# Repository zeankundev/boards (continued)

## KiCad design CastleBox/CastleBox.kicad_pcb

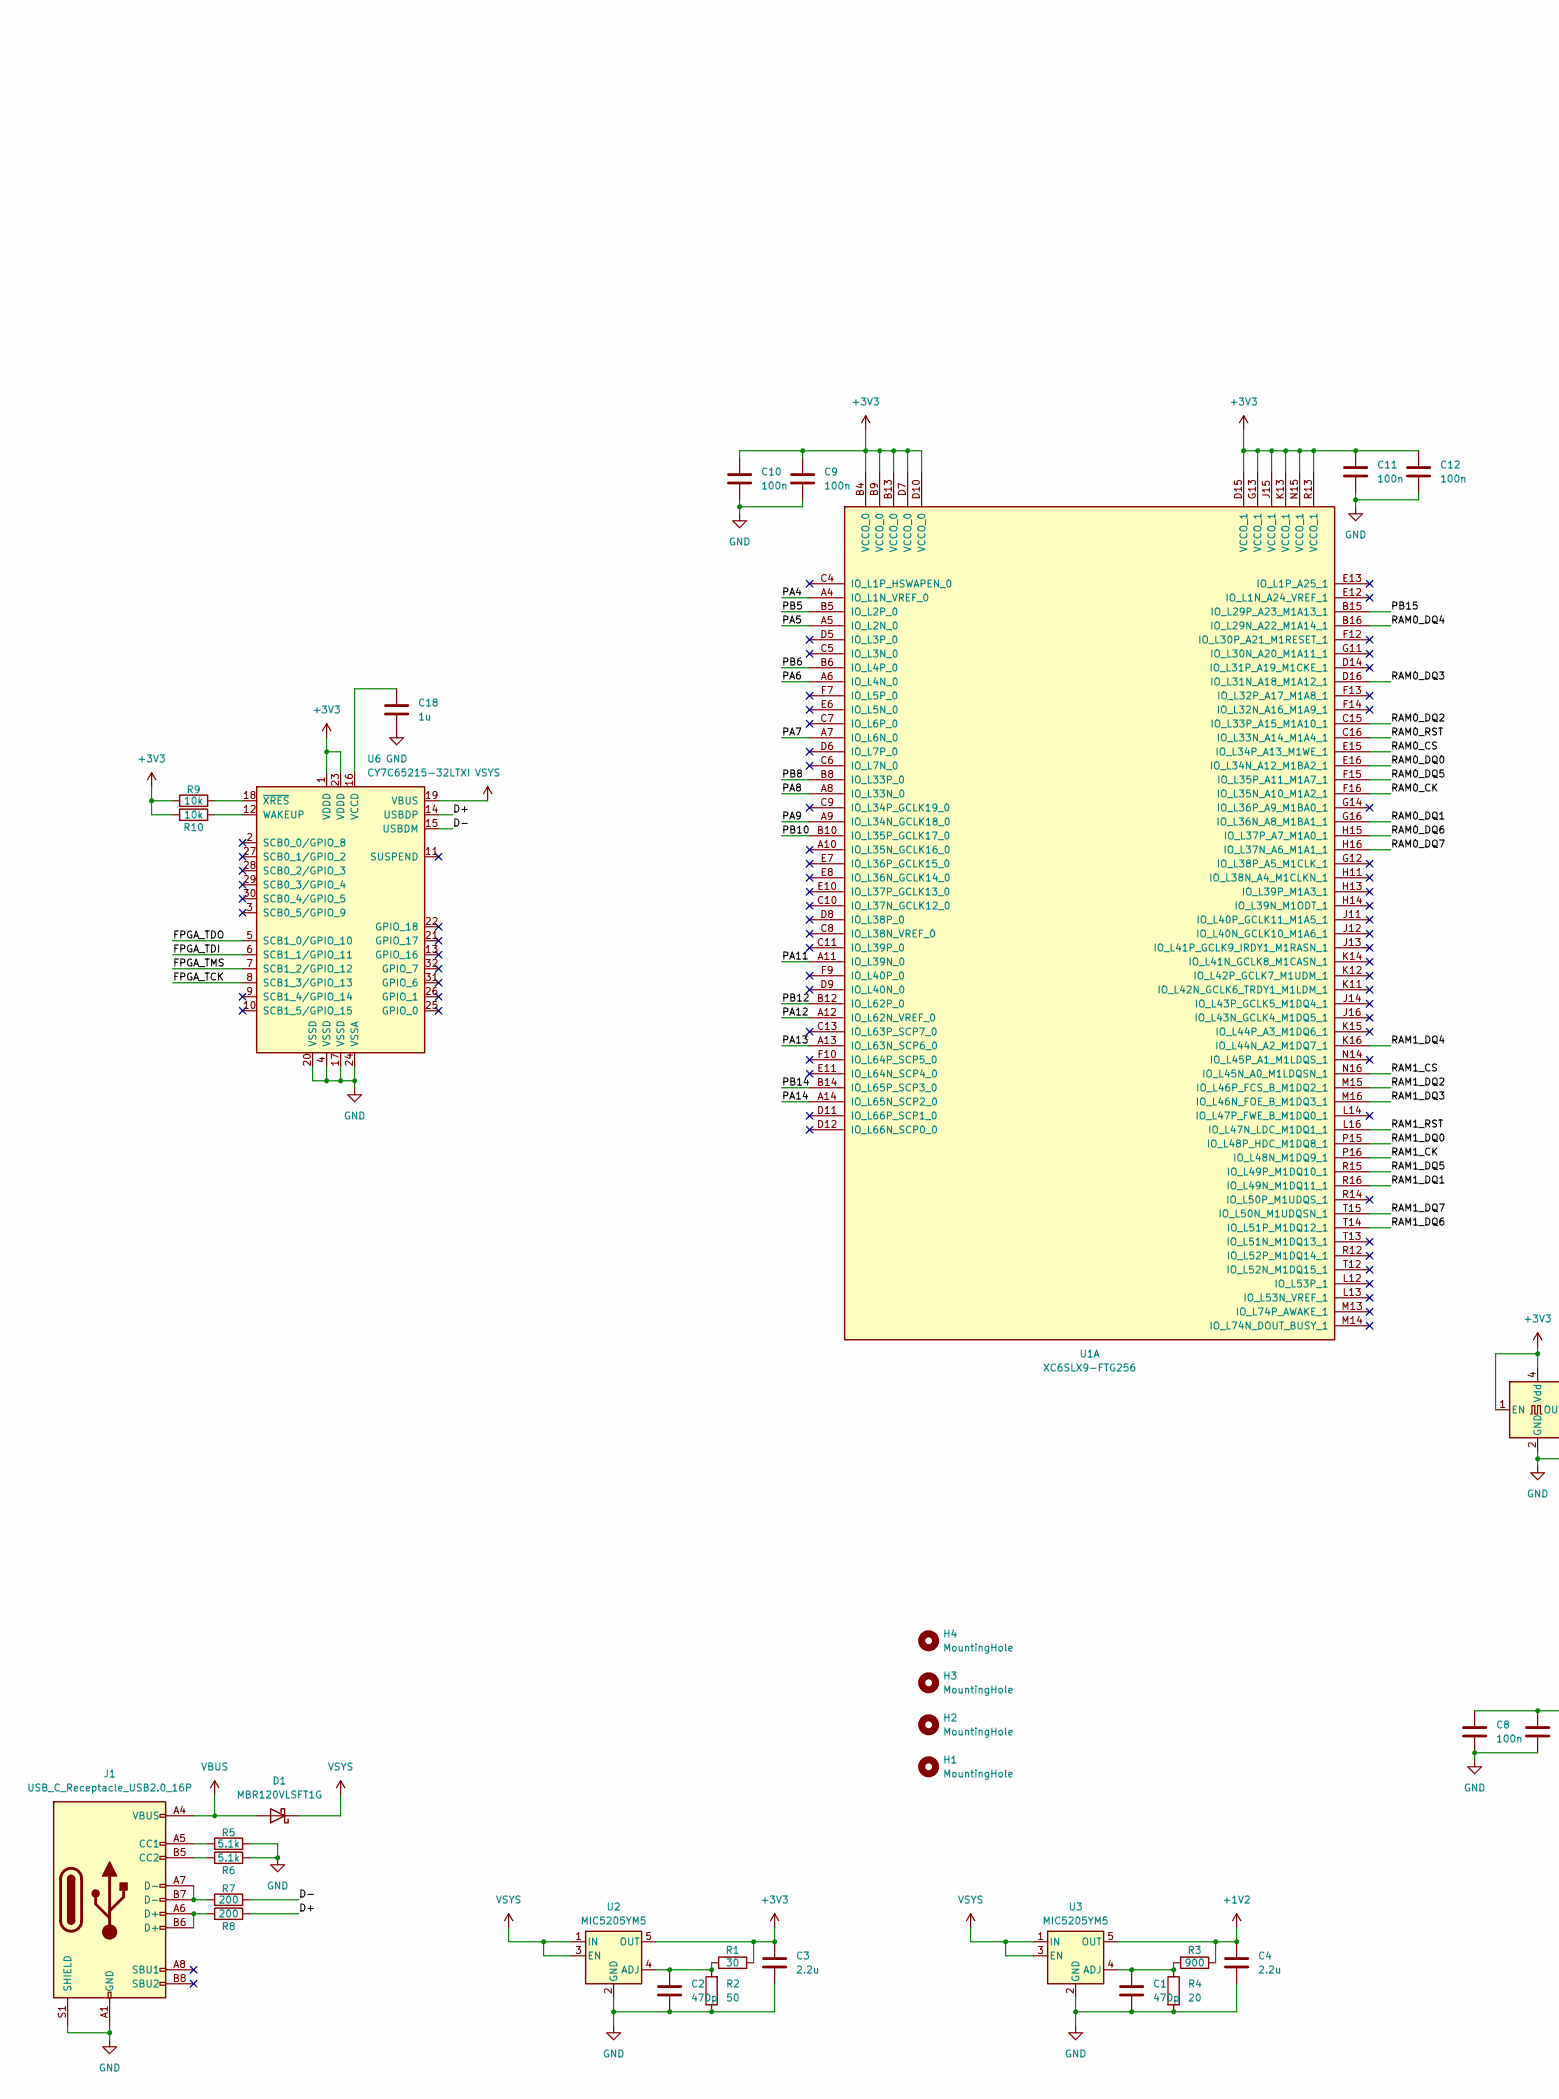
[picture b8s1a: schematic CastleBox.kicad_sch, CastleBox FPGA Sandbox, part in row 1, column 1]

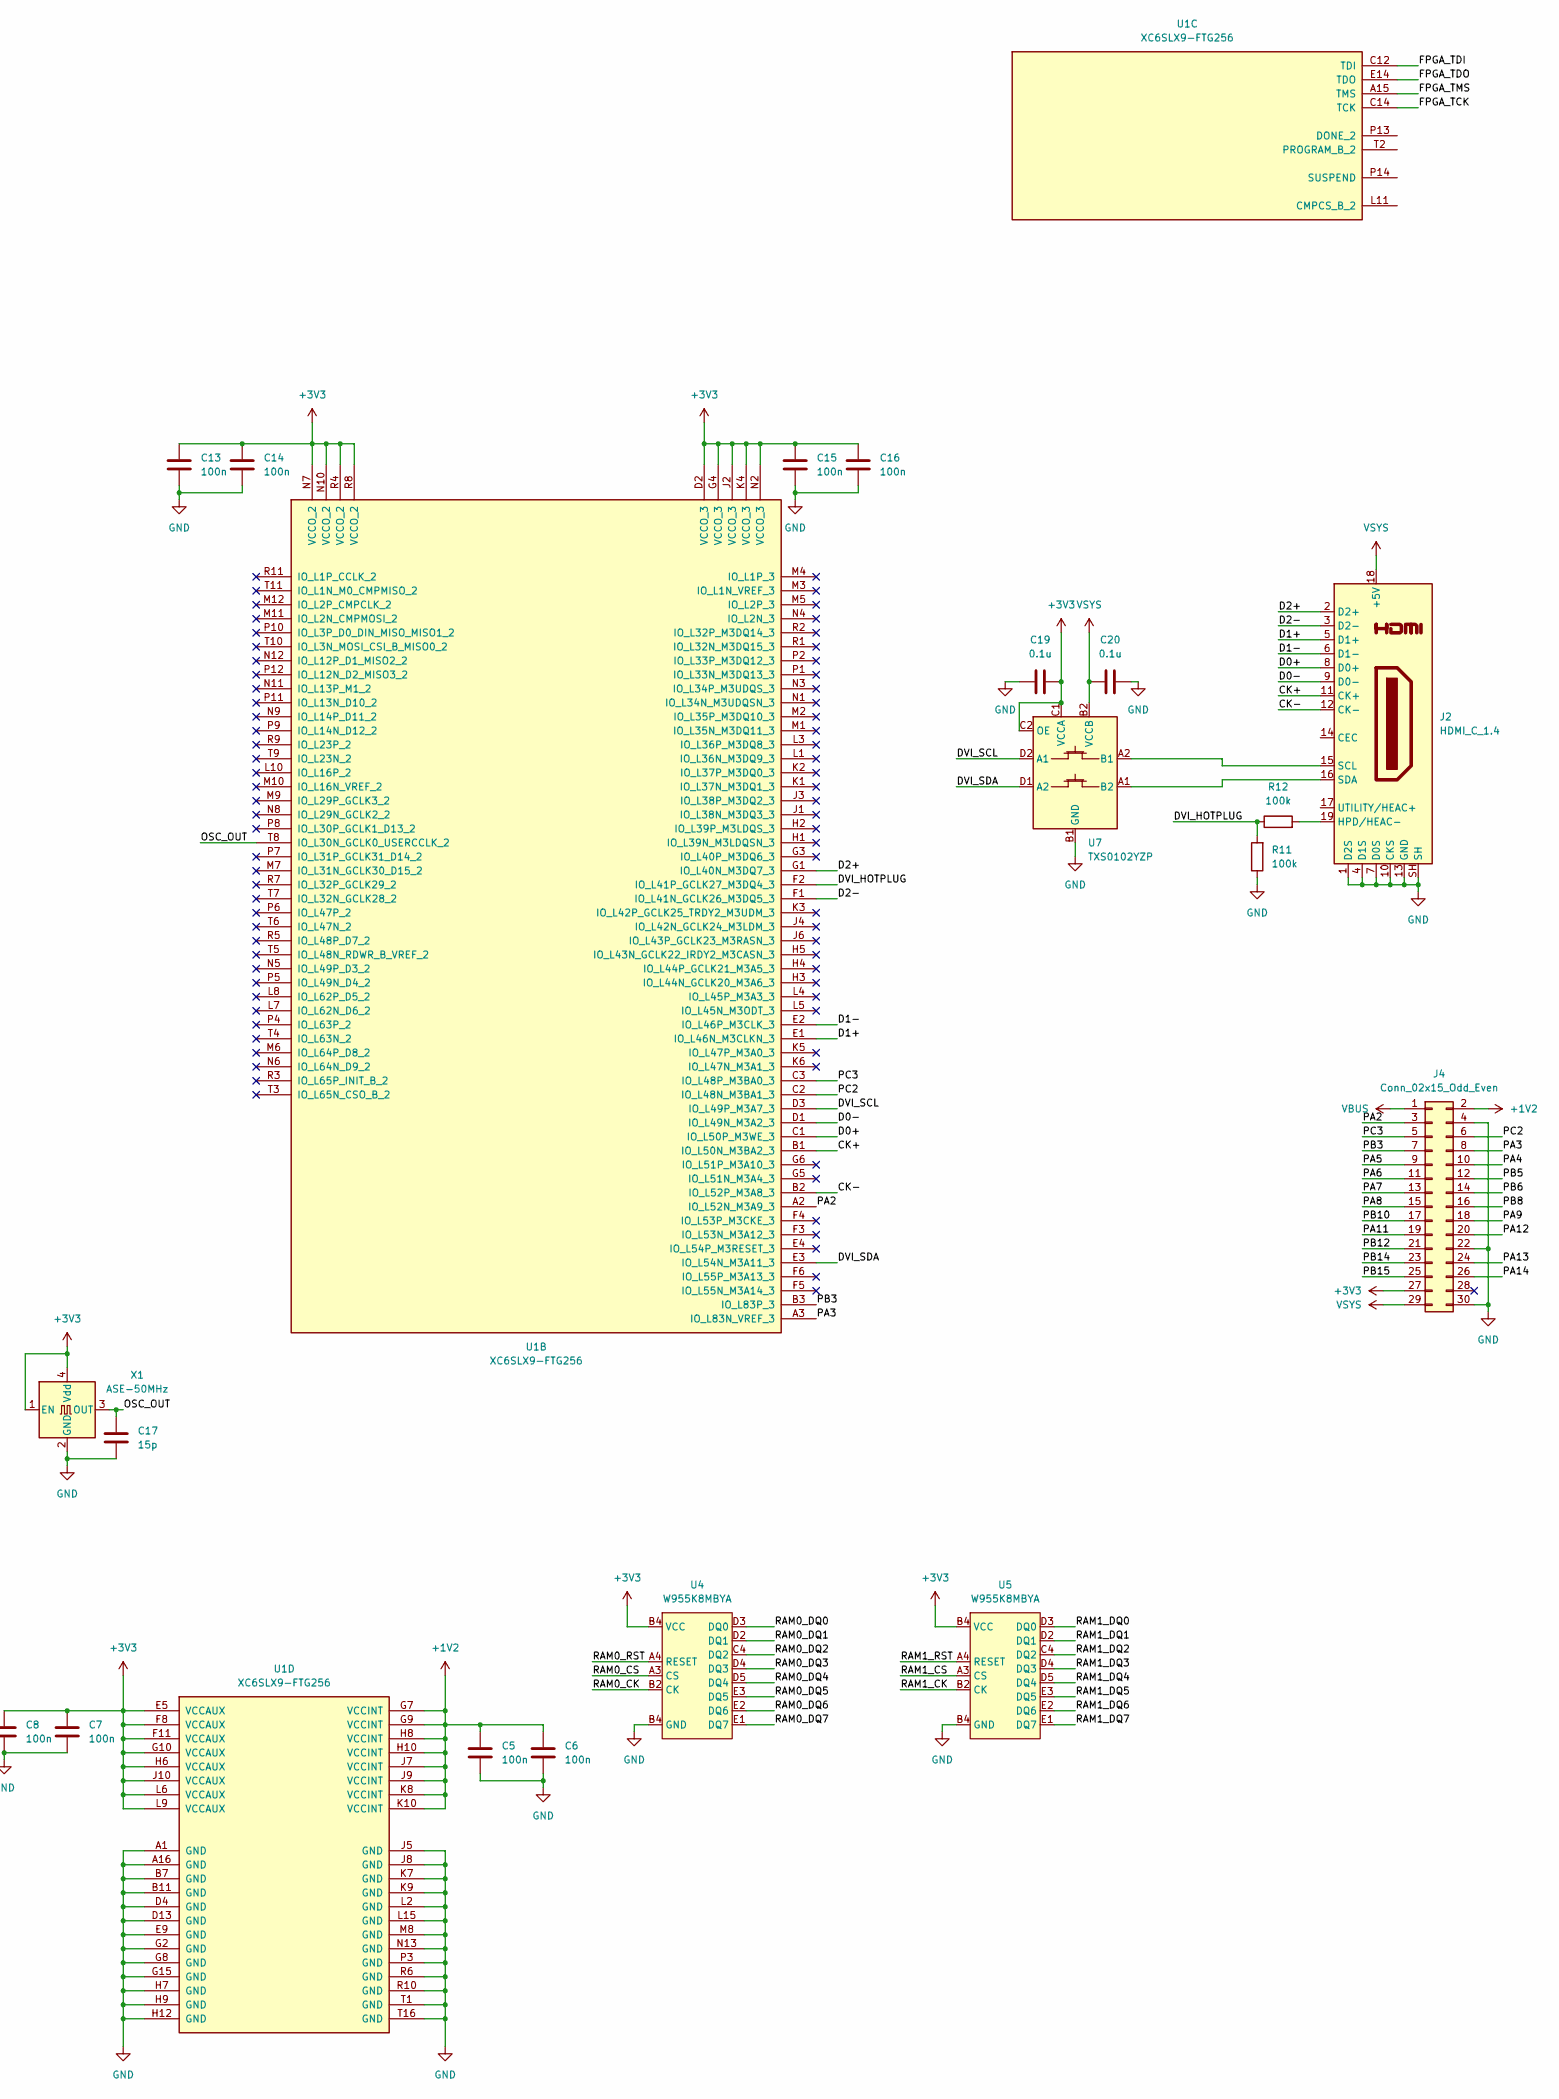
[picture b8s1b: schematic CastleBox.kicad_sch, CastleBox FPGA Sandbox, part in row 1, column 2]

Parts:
C1, C2: 470p; C_0402_1005Metric
C3, C4: 2.2u; C_0402_1005Metric
C5, C6, C7, C8, C9, C10, C11, C12, C13, C14, C15, C16: 100n; C_0402_1005Metric
C17: 15p; C_0402_1005Metric
C18: 1u; C_0402_1005Metric
C19, C20: 0.1u; C_0402_1005Metric
D1: MBR120VLSFT1G; D_SOD-123F
H1, H2, H3, H4: MountingHole; MountingHole_2.1mm
J1: USB_C_Receptacle_USB2.0_16P; USB_C_Receptacle_GCT_USB4105-xx-A_16P_TopMnt_Horizontal
J2: HDMI_C_1.4; VALCON_HD-RA-DSF12-TR
J4: Conn_02x15_Odd_Even; PinHeader_2x15_P2.54mm_Vertical
R1: 30; R_0402_1005Metric
R2: 50; R_0402_1005Metric
R3: 900; R_0402_1005Metric
R4: 20; R_0402_1005Metric
R5, R6: 5.1k; R_0402_1005Metric
R7, R8: 200; R_0402_1005Metric
R9, R10: 10k; R_0402_1005Metric
R11, R12: 100k; R_0402_1005Metric
U1: XC6SLX9-FTG256; BGA-256_17.0x17.0mm_Layout16x16_P1.0mm_Ball0.5mm_Pad0.4mm_N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
U2, U3: MIC5205YM5; SOT-23-5
U4, U5: W955K8MBYA
U6: CY7C65215-32LTXI; QFN-32-1EP_5x5mm_P0.5mm_EP3.45x3.45mm
U7: TXS0102YZP; Texas_DSBGA-8_0.9x1.9mm_Layout2x4_P0.5mm
X1: ASE-50MHz; Oscillator_SMD_Abracon_ASE-4Pin_3.2x2.5mm

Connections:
+1V2: C4.1, C5.1, C6.1, J4.2, R3.1, U1.G7 (VCCINT), U1.G9 (VCCINT), U1.H8 (VCCINT), U1.H10 (VCCINT), U1.J7 (VCCINT), U1.J9 (VCCINT), U1.K8 (VCCINT), U1.K10 (VCCINT), U3.5 (OUT)
/CK+: J2.11 (CK+), U1.B1 (IO_L50N_M3BA2_3)
/CK-: J2.12 (CK-), U1.B2 (IO_L52P_M3A8_3)
/D0+: J2.8 (D0+), U1.C1 (IO_L50P_M3WE_3)
/D0-: J2.9 (D0-), U1.D1 (IO_L49N_M3A2_3)
/D1+: J2.5 (D1+), U1.E1 (IO_L46N_M3CLKN_3)
/D1-: J2.6 (D1-), U1.E2 (IO_L46P_M3CLK_3)
/D2+: J2.2 (D2+), U1.G1 (IO_L40N_M3DQ7_3)
/D2-: J2.3 (D2-), U1.F1 (IO_L41N_GCLK26_M3DQ5_3)
/D+: R8.2, U6.14 (USBDP)
/D-: R7.2, U6.15 (USBDM)
/DVI_HOTPLUG: R11.2, R12.1, U1.F2 (IO_L41P_GCLK27_M3DQ4_3)
/DVI_SCL: U1.D3 (IO_L49P_M3A7_3), U7.D2 (A1)
/DVI_SDA: U1.E3 (IO_L54N_M3A11_3), U7.D1 (A2)
/FPGA_TCK: U1.C14 (TCK), U6.8 (SCB1_3/GPIO_13)
/FPGA_TDI: U1.C12 (TDI), U6.6 (SCB1_1/GPIO_11)
/FPGA_TDO: U1.E14 (TDO), U6.5 (SCB1_0/GPIO_10)
/FPGA_TMS: U1.A15 (TMS), U6.7 (SCB1_2/GPIO_12)
/OSC_OUT: C17.1, U1.T8 (IO_L30N_GCLK0_USERCCLK_2), X1.3 (OUT)
/PA2: J4.3, U1.A2 (IO_L52N_M3A9_3)
/PA3: J4.8, U1.A3 (IO_L83N_VREF_3)
/PA4: J4.10, U1.A4 (IO_L1N_VREF_0)
/PA5: J4.9, U1.A5 (IO_L2N_0)
/PA6: J4.11, U1.A6 (IO_L4N_0)
/PA7: J4.13, U1.A7 (IO_L6N_0)
/PA8: J4.15, U1.A8 (IO_L33N_0)
/PA9: J4.18, U1.A9 (IO_L34N_GCLK18_0)
/PA11: J4.19, U1.A11 (IO_L39N_0)
/PA12: J4.20, U1.A12 (IO_L62N_VREF_0)
/PA13: J4.24, U1.A13 (IO_L63N_SCP6_0)
/PA14: J4.26, U1.A14 (IO_L65N_SCP2_0)
/PB3: J4.7, U1.B3 (IO_L83P_3)
/PB5: J4.12, U1.B5 (IO_L2P_0)
/PB6: J4.14, U1.B6 (IO_L4P_0)
/PB8: J4.16, U1.B8 (IO_L33P_0)
/PB10: J4.17, U1.B10 (IO_L35P_GCLK17_0)
/PB12: J4.21, U1.B12 (IO_L62P_0)
/PB14: J4.23, U1.B14 (IO_L65P_SCP3_0)
/PB15: J4.25, U1.B15 (IO_L29P_A23_M1A13_1)
/PC2: J4.6, U1.C2 (IO_L48N_M3BA1_3)
/PC3: J4.5, U1.C3 (IO_L48P_M3BA0_3)
/RAM0_CK: U1.F16 (IO_L35N_A10_M1A2_1), U4.B2 (CK)
/RAM0_CS: U1.E15 (IO_L34P_A13_M1WE_1), U4.A3 (CS)
/RAM0_DQ0: U1.E16 (IO_L34N_A12_M1BA2_1), U4.D3 (DQ0)
/RAM0_DQ1: U1.G16 (IO_L36N_A8_M1BA1_1), U4.D2 (DQ1)
/RAM0_DQ2: U1.C15 (IO_L33P_A15_M1A10_1), U4.C4 (DQ2)
/RAM0_DQ3: U1.D16 (IO_L31N_A18_M1A12_1), U4.D4 (DQ3)
/RAM0_DQ4: U1.B16 (IO_L29N_A22_M1A14_1), U4.D5 (DQ4)
/RAM0_DQ5: U1.F15 (IO_L35P_A11_M1A7_1), U4.E3 (DQ5)
/RAM0_DQ6: U1.H15 (IO_L37P_A7_M1A0_1), U4.E2 (DQ6)
/RAM0_DQ7: U1.H16 (IO_L37N_A6_M1A1_1), U4.E1 (DQ7)
/RAM0_RST: U1.C16 (IO_L33N_A14_M1A4_1), U4.A4 (RESET)
/RAM1_CK: U1.P16 (IO_L48N_M1DQ9_1), U5.B2 (CK)
/RAM1_CS: U1.N16 (IO_L45N_A0_M1LDQSN_1), U5.A3 (CS)
/RAM1_DQ0: U1.P15 (IO_L48P_HDC_M1DQ8_1), U5.D3 (DQ0)
/RAM1_DQ1: U1.R16 (IO_L49N_M1DQ11_1), U5.D2 (DQ1)
/RAM1_DQ2: U1.M15 (IO_L46P_FCS_B_M1DQ2_1), U5.C4 (DQ2)
/RAM1_DQ3: U1.M16 (IO_L46N_FOE_B_M1DQ3_1), U5.D4 (DQ3)
/RAM1_DQ4: U1.K16 (IO_L44N_A2_M1DQ7_1), U5.D5 (DQ4)
/RAM1_DQ5: U1.R15 (IO_L49P_M1DQ10_1), U5.E3 (DQ5)
/RAM1_DQ6: U1.T14 (IO_L51P_M1DQ12_1), U5.E2 (DQ6)
/RAM1_DQ7: U1.T15 (IO_L50N_M1UDQSN_1), U5.E1 (DQ7)
/RAM1_RST: U1.L16 (IO_L47N_LDC_M1DQ1_1), U5.A4 (RESET)
unnamed: J1.A5 (CC1), R5.1
unnamed: J1.B5 (CC2), R6.1
unnamed: J1.A6 (D+), J1.B6 (D+), R8.1
unnamed: J1.A7 (D-), J1.B7 (D-), R7.1
unnamed: J2.19 (HPD/HEAC-), R12.2
unnamed: J2.15 (SCL), U7.A2 (B1)
unnamed: J2.16 (SDA), U7.A1 (B2)
unnamed: C2.1, R1.1, R2.2, U2.4 (ADJ)
unnamed: C1.1, R3.2, R4.1, U3.4 (ADJ)
unnamed: C18.1, U6.16 (VCCD)
unnamed: R10.2, U6.12 (WAKEUP)
unnamed: R9.2, U6.18 (~XRES)
VBUS: D1.2 (A), J1.A4 (VBUS), J1.A9 (VBUS), J1.B4 (VBUS), J1.B9 (VBUS), J4.1
VSYS: C20.1, D1.1 (K), J2.18 (+5V), J4.29, U2.1 (IN), U2.3 (EN), U3.1 (IN), U3.3 (EN), U6.19 (VBUS), U7.B2 (VCCB)

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
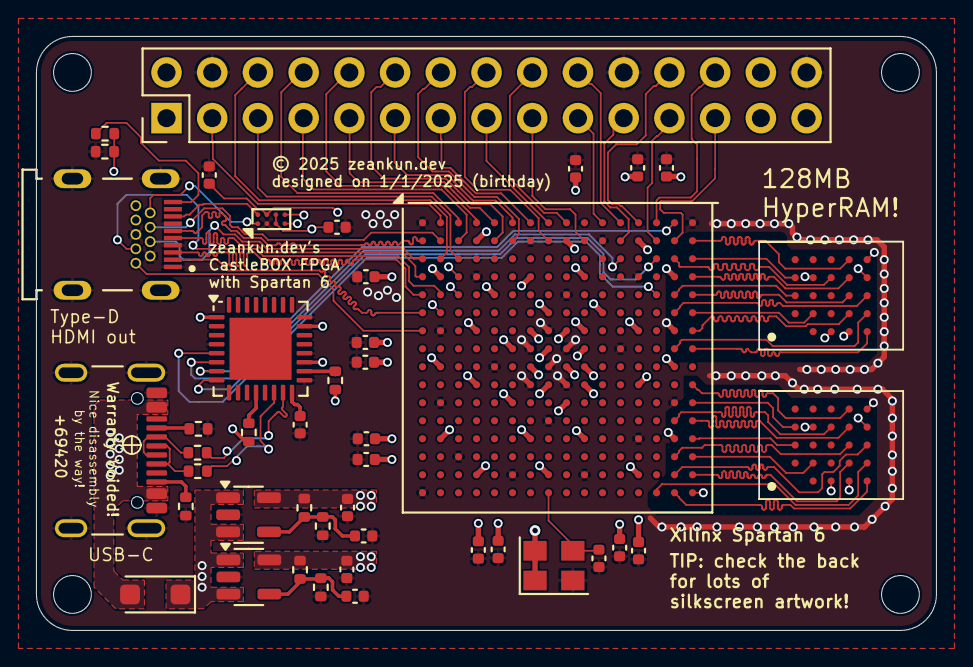
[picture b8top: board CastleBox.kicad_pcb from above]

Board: 6 copper layers, 50.0 x 33.0 mm, 48 parts (0 on the bottom side), 79 nets.

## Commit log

2024-10-15 first sync
2024-10-15 add more stitching vias
2024-10-15 forgor to delete lockfile
2024-10-15 ignored lockfiles
2024-10-15 made the stiching vias less denser (i509VCB)
2024-10-23 fix disconnection because of stitching vias that retards ask for repetitively
2024-11-01 add new boards
2024-12-18 fucked BB converter attempt
2024-12-26 add fpga board and tutorial pcb and more stuff
2025-01-04 routine backup
2025-01-11 fuck it, just delay it
2025-02-02 add more stuff
2025-02-03 fixed drc errors
2025-03-06 synced backup 6/3/2025
2025-05-20 sync to upstream 21/5/2025 06:52
2025-05-21 added castlebox neopro as well as qpush.sh for faster upstream commit
2025-05-21 added CastleBox NeoPro
2025-05-23 added SPI communication protocol
